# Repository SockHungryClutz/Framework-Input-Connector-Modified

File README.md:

# Framework input shim

**This repository is a fork of [CRImier/MyKiCad/.../framework_input_brkt_smol/](https://github.com/CRImier/MyKiCad/tree/master/Laptop%20mods/framework_input_brkt_smol)**  
(It was created as a new repo so as not to copy all other KiCad projects from CRImier in the same repo)

This is a small shim for the Framework laptop motherboard. It exposes the power button,
a USB port with 5V power, keyboard backlight, Caps Lock and fingerprint LED connections.
It is designed to fit inside the outline of the input connector FPC plug,
within the motherboard outline, so that it can easily be added to existing designs.

For wire connections, this shim uses THT holes, since it's relatively easy to rip
an SMD pad off the board by pulling on a wire. With the holes positioned out from behind the
mezzanine connector, this does not require any kapton tape fix or special assembly.

Markings on the PCB: "FrmW input brkt" (shortened because the board has to be very small)

Connector used: Amphenol 10156001-051100LF

These are KiCad 9 files as these were edited with the latest version

# Changes in v3.1:

- Updated to KiCad 9
- Moved THT holes out from behind connector to eliminate all chances of THT-to-connector shorts
- Increased board height to ~10mm to make room for THT (and some PCB services require at least 1cm board size in each dimension for assembly)
- Adjust silkscreens a bit, hopefully the meaning of labels is still clear

# Changes in v3:

- Updated to KiCad 6
- Updated soldermask on connector soldering layer to decrease chances of THT-to-connector shorts
- Cosmetic: removed between-pin traces on a GND group of pins
- Adjusted traces so that there's less visual "shorts"

# Changes in v2: 

The input connector symbol numbering was incorrect
and v1 of this adapter could break your mobo or something.

- Signal names are silkscreened on the board's top layers.

- Software: Kicad 6
- Version: 2
- PCB size: 18x7.75
- Layer count: 2

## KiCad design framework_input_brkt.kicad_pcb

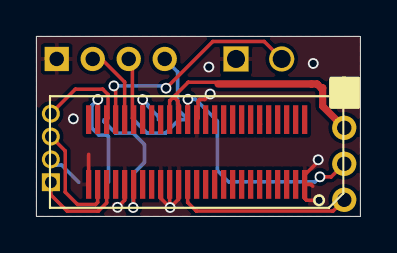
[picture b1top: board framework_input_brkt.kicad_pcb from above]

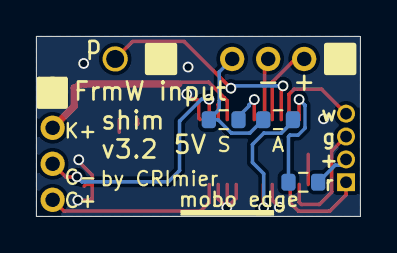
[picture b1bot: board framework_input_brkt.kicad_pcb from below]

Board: 2 copper layers, 18.0 x 10.0 mm, 8 parts (7 on the bottom side), 15 nets.

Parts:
J1: FPR_LED; PinHeader_1x04_P1.27mm_Vertical
J2: fpc_input_conn; Amphenol_10156001
J3: PWRSW; PinHeader_1x02_P2.54mm_Vertical
J4: USB; PinHeader_1x04_P2.00mm_Vertical
J5: KnC; PinHeader_1x04_P2.00mm_Vertical
R1: 0R; R_0603_1608Metric
R2: NC; R_0603_1608Metric
R3: 560R; R_0603_1608Metric

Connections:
/5VALW: J2.31, R2.2
/5VS: J2.19, R1.1
/CAPS_N: J2.14, J5.3
/CAPS_P_5V: J2.37, J5.4
/FPR_LED_COM_5V: J2.24, R3.1
/FPR_LED_G: J1.3, J2.27
/FPR_LED_R: J1.1, J2.28
/FPR_LED_W: J1.4, J2.23
/KBL_P: J2.15, J2.16, J5.2
/SWITCH: J2.22, J3.2
/USB_N: J2.20, J4.3
/USB_P: J2.21, J4.2
GND: J2.13, J2.26, J2.30, J2.34, J2.35, J2.36, J2.50, J3.1, J4.1, J5.1
unnamed: J1.2, R3.2
unnamed: J4.4, R1.2, R2.1

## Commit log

2026-04-14 Add files
    Hopefully this is all files needed for the project
2026-04-14 Added original/fork attribution
2026-04-15 Keep more of original design, only move the central through holes
2026-04-15 Ensure all files are updated
